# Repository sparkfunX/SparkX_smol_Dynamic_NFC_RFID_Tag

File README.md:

# SparkX smôl Dynamic NFC/RFID Tag

[*SparkX smôl Dynamic NFC/RFID Tag (SPX-18991)*](https://www.sparkfun.com/products/18991)

You might be wondering why we would make an NFC/RFID tag peripheral board for smôl? The STMicroelectronics ST25FV64KC is a _**dynamic**_ Near Frequency Communication / Radio Frequency Identification tag IC with 64Kbit (8KByte) of on-board EEPROM memory. It has an I<sup>2</sup>C interface which the smôl processor board can use to read and write to the EEPROM memory. But the memory can also be read and written to over the RF link _while your smôl ecosystem is in deep sleep_! This means it is perfect for: contactless data storage and collection; and for configuration.

## Repository Contents

- **/Hardware** - Eagle design files
- **LICENSE.md** contains the licence information

## Product Versions

- [SPX-18991](https://www.sparkfun.com/products/18991) - Original SparkX Release.

## License Information

This product is _**open source**_!

Please review the LICENSE.md file for license information.

If you have any questions or concerns on licensing, please contact technical support on our [SparkFun forums](https://forum.sparkfun.com/viewforum.php?f=123).

Distributed as-is; no warranty is given.

- Your friends at SparkFun.

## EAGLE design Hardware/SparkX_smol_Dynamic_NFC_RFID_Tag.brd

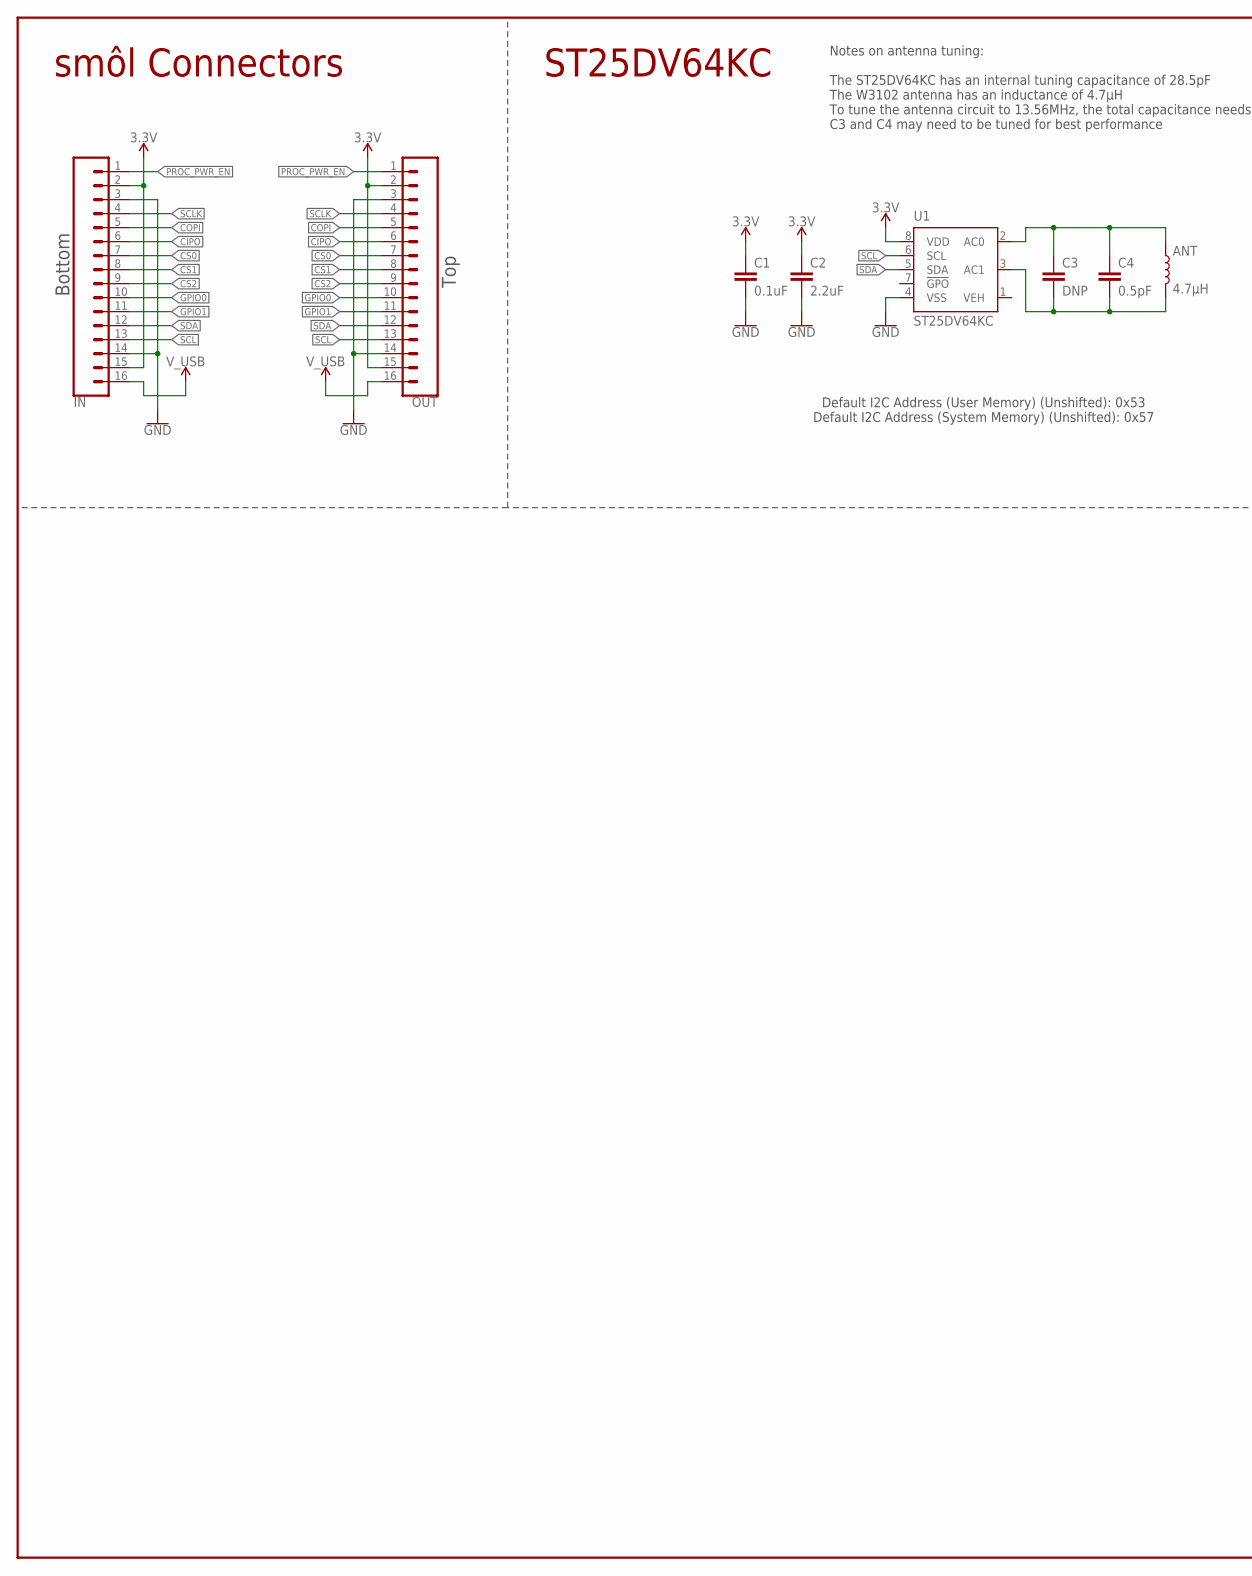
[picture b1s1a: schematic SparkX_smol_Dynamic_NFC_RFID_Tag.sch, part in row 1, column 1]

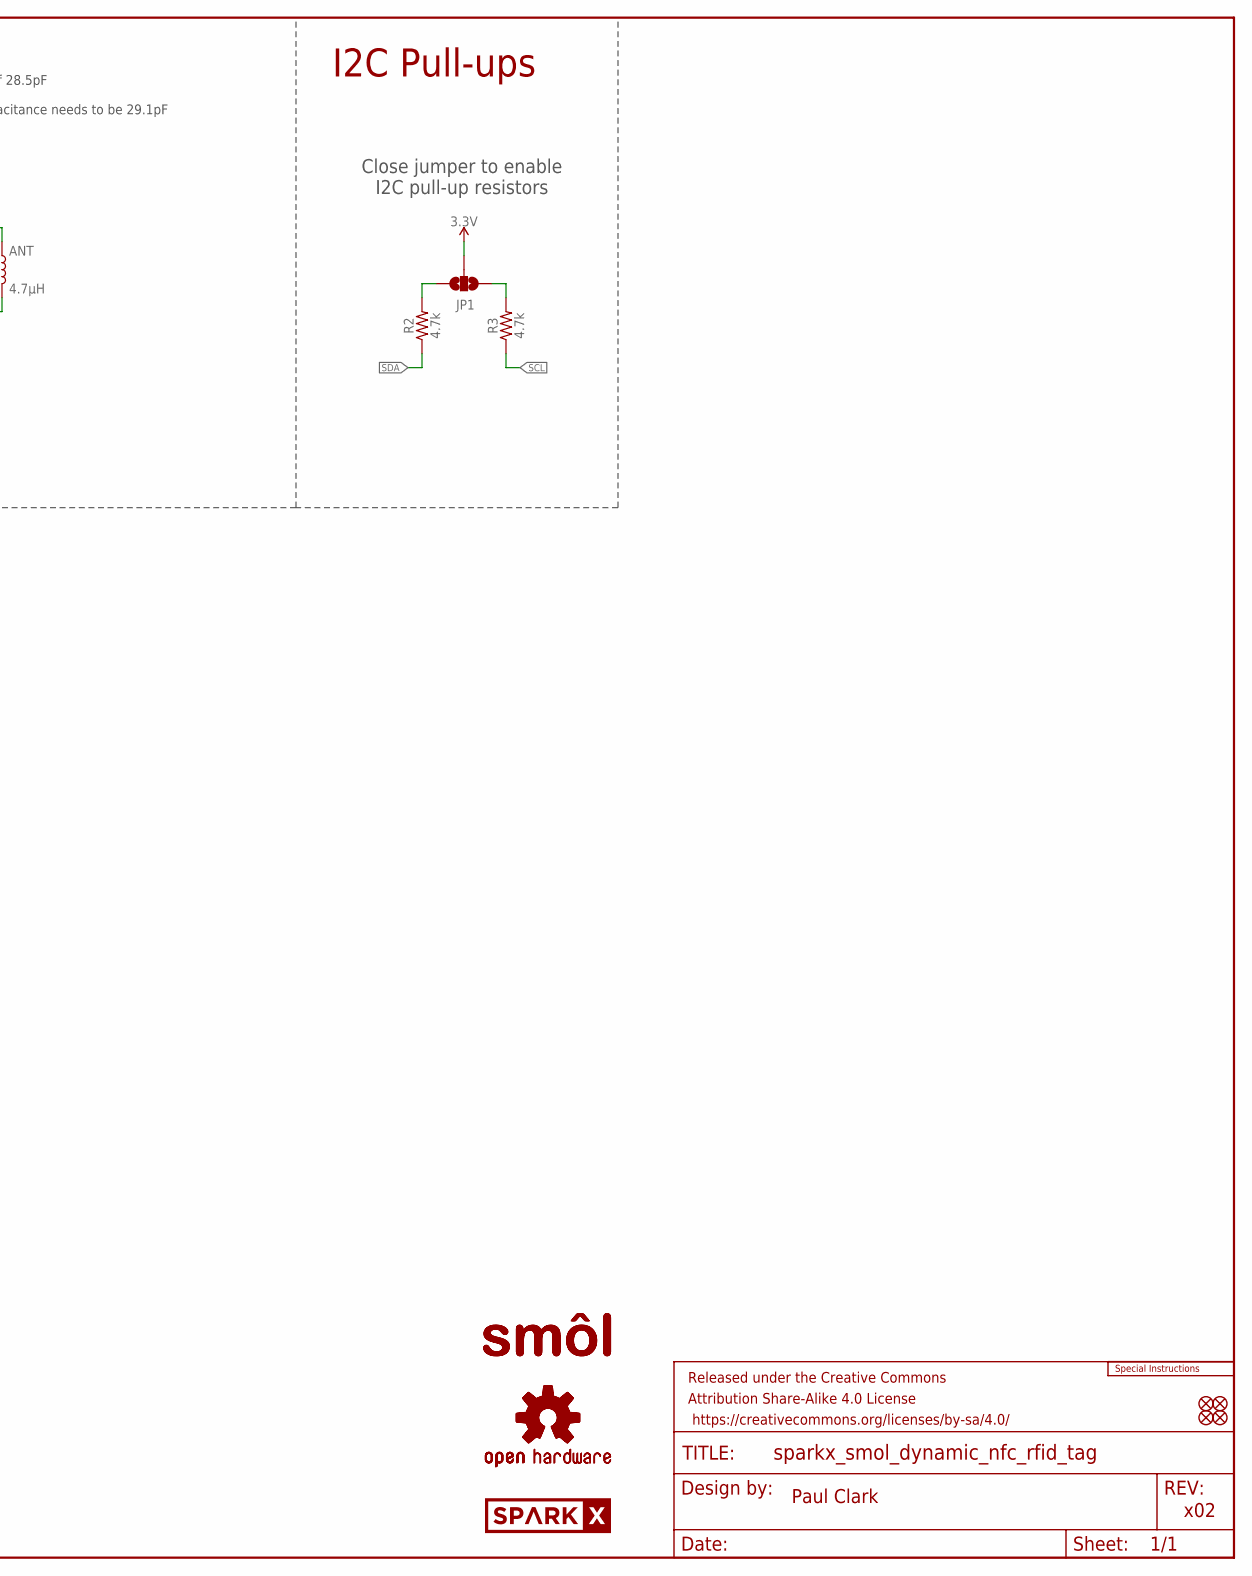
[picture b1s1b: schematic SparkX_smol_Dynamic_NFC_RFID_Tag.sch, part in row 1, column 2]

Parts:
ANT: 4.7μH; W3102
C1: 0.1uF; 0402-TIGHT
C2: 2.2uF; 0402-TIGHT
C3: DNP; 0402-TIGHT_NO_CREAM
C4: 0.5pF; 0402-TIGHT
FD1, FD2, FD3, FD4: FIDUCIALUFIDUCIAL; FIDUCIAL-MICRO
FRAME1: FRAME-LEDGER; CREATIVE_COMMONS
IN: CONN_16FPC_16_0.5MM; FPC_16_0.5MM
JP1: JUMPER-SMT_3_NO_SILK; SMT-JUMPER_3_NO_SILK
LOGO1: SPECIAL_INSTRUCTIONS-ORDERING; ORDERING_INSTRUCTIONS
LOGO2, LOGO3: OSHW-LOGOMINI; OSHW-LOGO-MINI
OUT: CONN_16FPC_16_0.5MM; FPC_16_0.5MM
R2, R3: 4.7k; 0402-TIGHT
U1: ST25DV64KC; SO08
U$1: SPARKX-LOGO3; SPARKX-SMALL
U$3, U$9: SMOL_LOGOSMALL; SMOL_SMALL

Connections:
3.3V: C1.1, C2.1, IN.2, IN.15, JP1.2, OUT.2, OUT.15, U1.8 (VDD)
CIPO: IN.6, OUT.6
COPI: IN.5, OUT.5
CS0: IN.7, OUT.7
CS1: IN.8, OUT.8
CS2: IN.9, OUT.9
GND: C1.2, C2.2, IN.3, IN.14, OUT.3, OUT.14, U1.4 (VSS)
GPIO0: IN.10, OUT.10
GPIO1: IN.11, OUT.11
unnamed: ANT.2, C3.2, C4.2, U1.3 (AC1)
unnamed: ANT.1, C3.1, C4.1, U1.2 (AC0)
unnamed: JP1.3, R2.2
unnamed: JP1.1, R3.2
PROC_PWR_EN: IN.1, OUT.1
SCL: IN.13, OUT.13, R3.1, U1.6 (SCL)
SCLK: IN.4, OUT.4
SDA: IN.12, OUT.12, R2.1, U1.5 (SDA)
VEH: U1.1 (VEH)
V_USB: IN.16, OUT.16

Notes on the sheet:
Paul Clark
x02
smôl Connectors
Top
Bottom
ST25DV64KC
Default I2C Address (User Memory) (Unshifted): 0x53 Default I2C Address (System Memory) (Unshifted): 0x57
Notes on antenna tuning: The ST25DV64KC has an internal tuning capacitance of 28.5pF The W3102 antenna has an inductance of 4.7µH To tune the antenna circuit to 13.56MHz, the total capacitance needs to be 29.1pF C3 and C4 may need to be tuned for best performance
Close jumper to enable I2C pull-up resistors
I2C Pull-ups

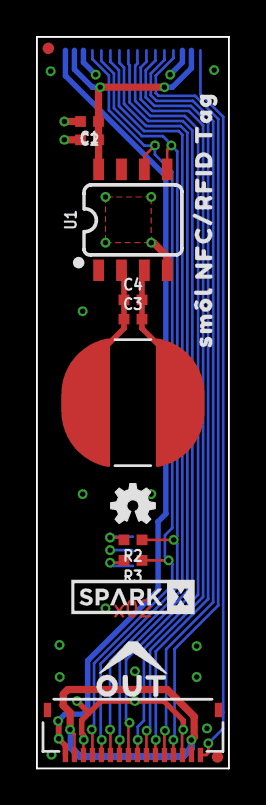
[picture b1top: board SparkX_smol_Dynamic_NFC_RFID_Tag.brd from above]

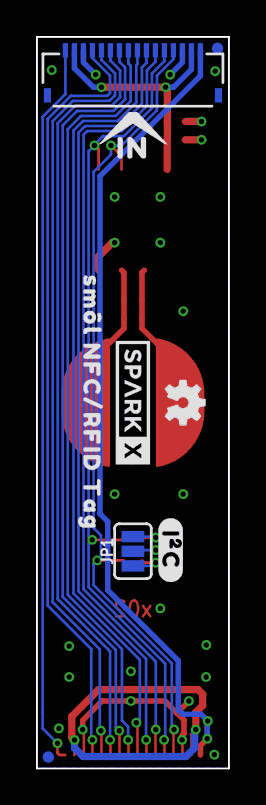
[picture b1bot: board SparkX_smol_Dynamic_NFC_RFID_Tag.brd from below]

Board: 4 copper layers, 10.7 x 40.6 mm, 28 parts (10 on the bottom side), 18 nets.

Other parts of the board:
U$2, U$4: SM�L_NFC#RFID_TAG0
U$5: #I�C#0
U$8: IN0
U$17: OUT0
U$20: SPARKX-LOGO3; SPARKX-SMALL

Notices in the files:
parts and their libraries:
SparkFun-Aesthetics: Licensing: Creative Commons ShareAlike 4.0 International - https://creativecommons.org/licenses/by-sa/4.0
SparkFun-Aesthetics: Released under the Creative Commons Attribution Share-Alike 4.0 License
SparkFun-Aesthetics: https://creativecommons.org/licenses/by-sa/4.0
